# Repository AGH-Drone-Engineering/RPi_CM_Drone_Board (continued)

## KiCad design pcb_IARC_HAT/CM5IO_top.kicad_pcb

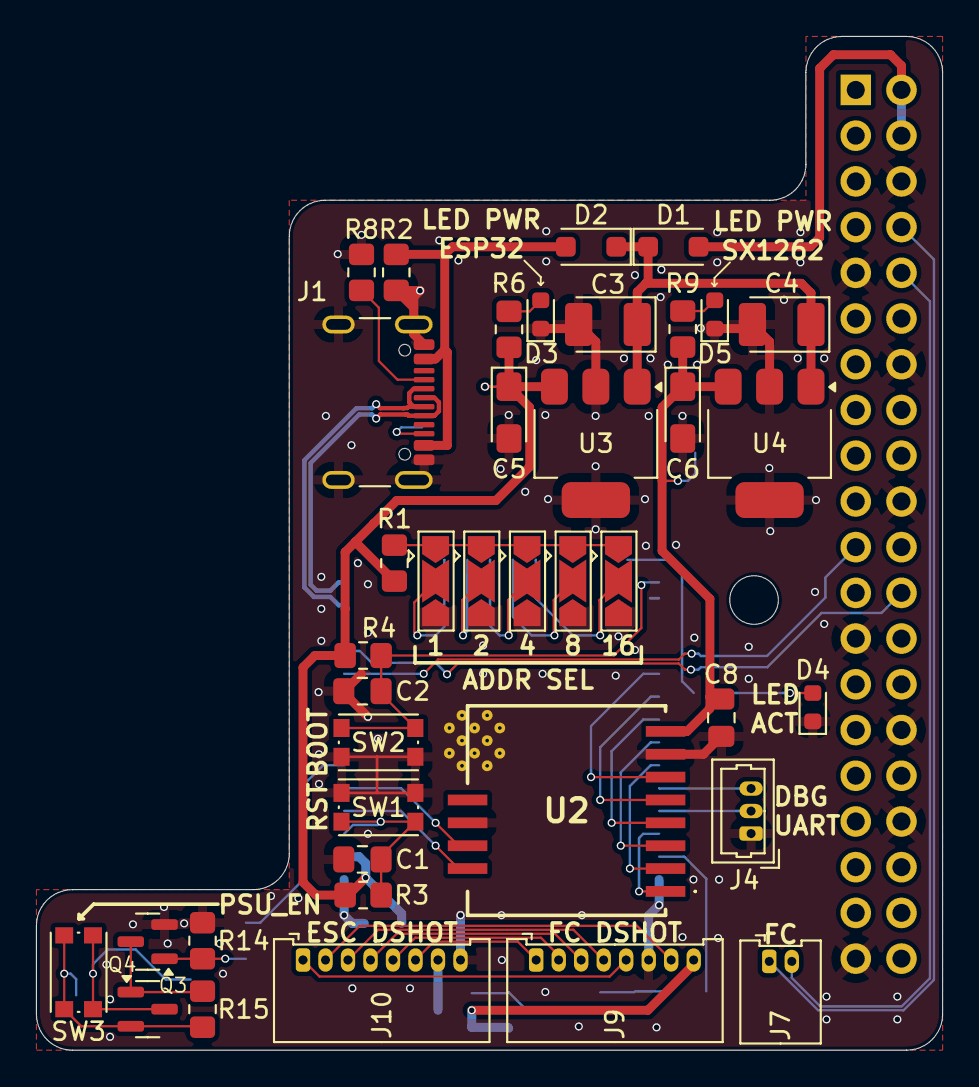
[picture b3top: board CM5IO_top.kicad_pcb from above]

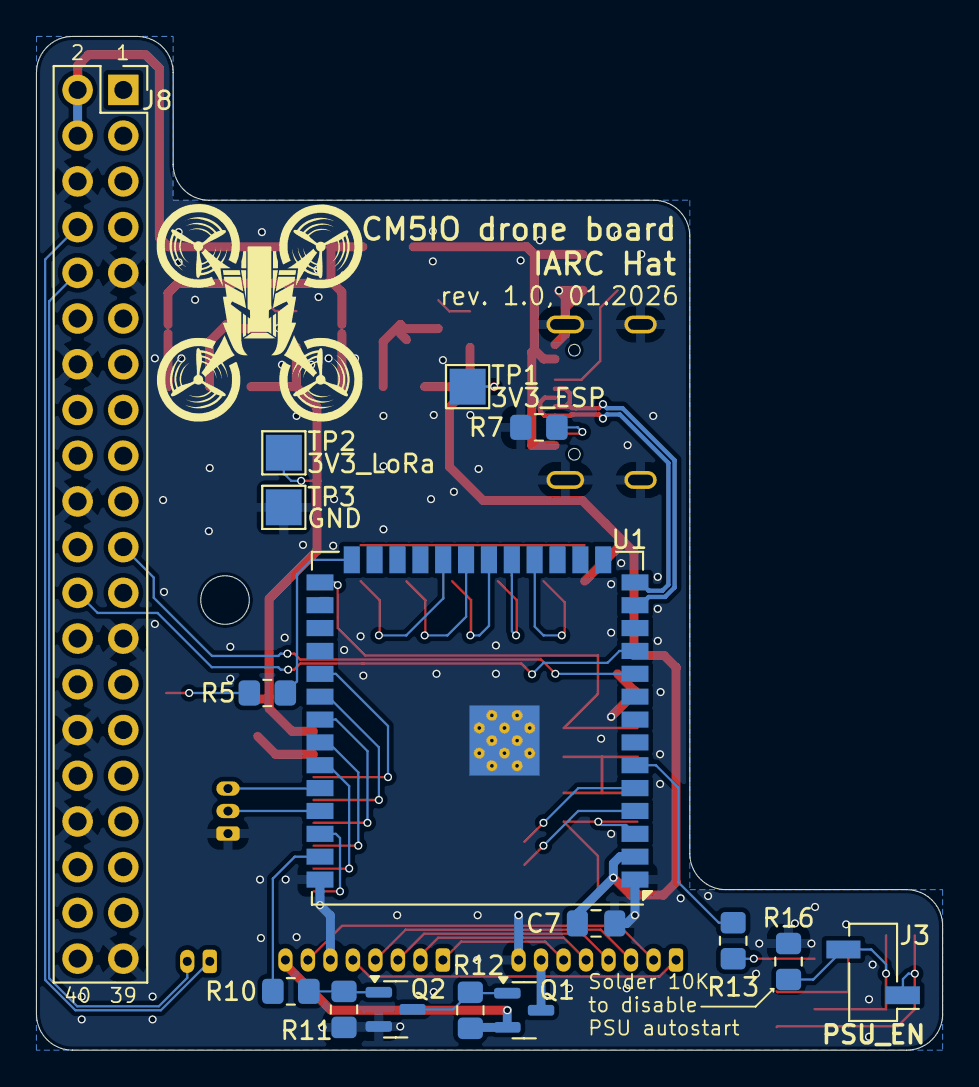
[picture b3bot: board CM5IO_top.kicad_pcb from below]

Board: 2 copper layers, 50.3 x 56.3 mm, 57 parts (16 on the bottom side), 52 nets.

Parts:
C1, C2, C7, C8: 470nF; C_0805_2012Metric_Pad1.18x1.45mm_HandSolder
C3, C4: 4.7uF 35v; CP_EIA-3528-21_Kemet-B_HandSolder
C5, C6: 4.7uF 10v; CP_EIA-3216-18_Kemet-A_HandSolder
D1, D2: MBR1020VL; D_SOD-123F
D3, D5: LED Red; LED_0603_1608Metric
D4: LED Green; LED_0603_1608Metric
H1: MountingHole; MountingHole_2.7mm_M2.5_DIN965
J1: USB_C_Receptacle_USB2.0; USB_C_Receptacle_GCT_USB4105-xx-A_16P_TopMnt_Horizontal
J3: J_PSU_EN; PinSocket_1x02_P2.54mm_Vertical_SMD_Pin1Left
J4: J_ESP_DBG_UART; Molex_PicoBlade_53047-0310_1x03_P1.25mm_Vertical
J7: J_FC_UART; Molex_PicoBlade_53048-0210_1x02_P1.25mm_Horizontal
J8: THD-20-R; PinSocket_2x20_P2.54mm_Vertical
J9: J_DShot600_ESC; Molex_PicoBlade_53048-0810_1x08_P1.25mm_Horizontal
J10: J_DShot600_FC; Molex_PicoBlade_53048-0810_1x08_P1.25mm_Horizontal
JP1: ADDR1; SolderJumper-3_P2.0mm_Open_TrianglePad1.0x1.5mm
JP2: ADDR2; SolderJumper-3_P2.0mm_Open_TrianglePad1.0x1.5mm
JP3: ADDR4; SolderJumper-3_P2.0mm_Open_TrianglePad1.0x1.5mm
JP4: ADDR8; SolderJumper-3_P2.0mm_Open_TrianglePad1.0x1.5mm
JP5: ADDR16; SolderJumper-3_P2.0mm_Open_TrianglePad1.0x1.5mm
Module1: ComputeModule5-CM5; Raspberry-Pi-5-Compute-Module
Q1, Q4: AO3401A; SOT-23
Q2, Q3: Q_NPN_BEC; SOT-23
R1, R3, R4, R5, R6, R9, R10, R12, R13, R15: 1K; R_0805_2012Metric_Pad1.20x1.40mm_HandSolder
R2: 2.2K 1%; R_0805_2012Metric_Pad1.20x1.40mm_HandSolder
R7, R8: 5.1K 1%; R_0805_2012Metric_Pad1.20x1.40mm_HandSolder
R11, R14, R16: 10K; R_0805_2012Metric_Pad1.20x1.40mm_HandSolder
SW1: SW_RESET; SW_Push_1P1T_NO_CK_KMR2
SW2: SW_BOOT; SW_Push_1P1T_NO_CK_KMR2
SW3: FORCE_PWR; SW_Push_1P1T_NO_CK_KMR2
TP1: 3V3_ESP; TestPoint_Pad_2.0x2.0mm
TP2: 3V3_LORA; TestPoint_Pad_2.0x2.0mm
TP3: GND; TestPoint_Pad_2.0x2.0mm
U1: ESP32-S3-WROOM-1; ESP32-S3-WROOM-1U
U2: Wio-SX1262
U3, U4: AP7361C-33E; SOT-223-3_TabPin2

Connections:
/+3.3v_ESP: C5.1, C7.2, R1.1, R3.1, R4.1, R6.1, TP1.1, U1.2 (3V3), U3.3 (VO)
/+3.3v_LoRa: C6.1, C8.2, R9.1, TP2.1, U2.8 (VCC), U4.3 (VO)
/+5v_RPi: D1.2 (A), J8.2, J8.4
/+5v_USB: D2.2 (A), J1.A4 (VBUS), J1.A9 (VBUS), J1.B4 (VBUS), J1.B9 (VBUS), R2.1
/Comm/ADDR1: JP1.2 (C), U1.18 (IO10)
/Comm/ADDR2: JP2.2 (C), U1.19 (IO11)
/Comm/ADDR4: JP3.2 (C), U1.20 (IO12)
/Comm/ADDR8: JP4.2 (C), U1.21 (IO13)
/Comm/ADDR16: JP5.2 (C), U1.22 (IO14)
/Comm/ADDR_HIGH: JP1.1 (A), JP2.1 (A), JP3.1 (A), JP4.1 (A), JP5.1 (A), R1.2
/Comm/BOOT_MODE: C2.2, R4.2, SW2.2, U1.27 (IO0)
/Comm/ENABLE: C1.2, R3.2, SW1.2, U1.3 (EN)
/Comm/KILLSWITCH_FC_CTL: R10.1, U1.39 (IO1)
/Comm/KILLSWITCH_PSU_CTL: R13.1, U1.6 (IO6)
/Comm/LED_ACT: R5.1, U1.26 (IO45)
/Comm/LORA_BUSY: U1.5 (IO5), U2.11 (BUSY)
/Comm/LORA_DIO1: U1.4 (IO4), U2.12 (DIO1)
/Comm/LORA_RESET: U1.32 (IO39), U2.5 (NRST)
/Comm/LORA_RF_SW: U1.38 (IO2), U2.1 (RF_SW_)
/Comm/LORA_SPI_CLK: U1.33 (IO40), U2.4 (SCK)
/Comm/LORA_SPI_CS: U1.31 (IO38), U2.6 (NSS)
/Comm/LORA_SPI_MISO: U1.35 (IO42), U2.2 (MISO)
/Comm/LORA_SPI_MOSI: U1.34 (IO41), U2.3 (MOSI)
/Dshot600_CURR: J9.5, J10.1
/Dshot600_M1: J9.4, J10.3
/Dshot600_M2: J9.3, J10.4
/Dshot600_M3: J9.2, J10.5
/Dshot600_M4: J9.1, J10.6
/Dshot600_R7: J9.7, J10.2
/ESP_USB2_N: J1.A7 (D-), J1.B7 (D-), U1.13 (USB_D-)
/ESP_USB2_P: J1.A6 (D+), J1.B6 (D+), U1.14 (USB_D+)
/GPIO8: J8.24, U1.11 (IO18)
/GPIO9: J8.21, U1.10 (IO17)
/GPIO14_UART_TX: J7.1, J8.8
/GPIO15_UART_RX: J7.2, J8.10
/PSU_CTL_EN: J3.2, Q4.3 (D), R16.1, SW3.1
/PSU_VIN: J3.1, Q4.2 (S), R15.1, SW3.2
/VBUS_ESC: J9.8, Q1.2 (S), R12.1
/VBUS_FC: J10.7, Q1.3 (D)
/VIN: C3.1, C4.1, D1.1 (K), D2.1 (K), U3.1 (VI), U4.1 (VI)
GND: C1.1, C2.1, C3.2, C4.2, C5.2, C6.2, C7.1, C8.1, D3.1 (K), D4.1 (K), D5.1 (K), J1.A1 (GND), J1.A12 (GND), J1.B1 (GND), J1.B12 (GND), J1.S1 (SHIELD), J4.1, J8.6, J8.9, J8.14, J8.20, J8.25, J8.30, J8.34, J8.39, J9.6, J10.8, JP1.3 (B), JP2.3 (B), JP3.3 (B), JP4.3 (B), JP5.3 (B), Q2.2 (E), Q3.2 (E), R2.2, R7.1, R8.1, R11.2, R14.2, R16.2, SW1.1, SW2.1, TP3.1, U1.1 (GND), U1.40 (GND), U1.41 (GND), U2.7 (GND_1), U2.10 (GND_2), U3.2 (GND), U4.2 (GND)
unnamed: D3.2 (A), R6.2
unnamed: D4.2 (A), R5.2
unnamed: D5.2 (A), R9.2
unnamed: J1.A5 (CC1), R8.2
unnamed: J1.B5 (CC2), R7.2
unnamed: J4.2, U1.37 (TXD0)
unnamed: J4.3, U1.36 (RXD0)
unnamed: Q1.1 (G), Q2.3 (C), R12.2
unnamed: Q2.1 (B), R10.2, R11.1
unnamed: Q3.1 (B), R13.2, R14.1
unnamed: Q3.3 (C), Q4.1 (G), R15.2

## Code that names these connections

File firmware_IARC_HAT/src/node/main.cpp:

#include <RFNode.h>
#include <cstring>
#include "UartRfBridge.h"

// Logger write function for USB-CDC (Serial) output.
static void logToUsbCdc(const char *str)
{
    Serial.print(str);
}

static const char *beginStatusToStr(BeginStatus bs)
{
    switch (bs)
    {
    case BeginStatus::OK:
        return "ok";
    case BeginStatus::ALREADY_STARTED:
        return "already_started";
    case BeginStatus::INVALID_CONFIG:
        return "invalid_config";
    case BeginStatus::SECURITY_INIT_FAILED:
        return "security_init_failed";
    case BeginStatus::RADIO_INIT_FAILED:
        return "radio_init_failed";
    case BeginStatus::OUT_OF_MEMORY:
        return "out_of_memory";
    case BeginStatus::NV_NOT_PERSISTENT:
        return "nv_not_persistent";
    case BeginStatus::NV_SEQ_CORRUPTED:
        return "nv_seq_corrupted";
    default:
        return "unknown";
    }
}

// LoRa module pinout on the IARC HAT (SX1262):
#define LORA_CS 38
#define LORA_IRQ 4
#define LORA_RST 39
#define LORA_BUSY 5

#define LORA_RF_SW 2
#define LORA_CLK 40
#define LORA_MOSI 41
#define LORA_MISO 42

// Killswitch pins
#define KILLSWITCH_FC_CTL 1
#define KILLSWITCH_PSU_CTL 6

// RPi <-> ESP link: hardware UART0 (Serial0), remapped off its default pins.
// The module's native TXD0/RXD0 (IO43/IO44, pads 37/36) go to J4
// (J_ESP_DBG_UART), not to the Pi - see pcb_IARC_HAT/comm.kicad_sch. The link
// to the host runs over the 40-pin header J8: net GPIO8 (header pin 24, the
// Pi's TXD3) lands on U1 pad 11 = IO18, and net GPIO9 (header pin 21, the Pi's
// RXD3) on U1 pad 10 = IO17. That is UART3 on the Pi, i.e. /dev/ttyAMA3, which
// is what loracom opens by default.
#define RPI_UART_TX 17
#define RPI_UART_RX 18
#define RPI_UART_BAUD 115200

#define KILL_PAYLOAD "KILL"
static constexpr size_t KILL_PAYLOAD_LEN = sizeof(KILL_PAYLOAD) - 1;

// Only the ground panel may kill
static constexpr uint8_t KILL_MASTER_ADDR = 0xFE;

// Node address is set by the five solder jumpers JP1..JP5 (schematic labels
// ADDR1/2/4/8/16, pcb_IARC_HAT/comm.kicad_sch), least significant bit first.
static const uint8_t ADDR_PINS[] = {10, 11, 12, 13, 14};
static constexpr size_t ADDR_BITS = sizeof(ADDR_PINS) / sizeof(ADDR_PINS[0]);

static SPIClass loraSPI;
static SX1262LoRaRadio radio(SX1262LoRaRadio::Channel::EU868_CH0,
                             LORA_CS, LORA_IRQ, LORA_RST, LORA_BUSY, loraSPI);

// addr is left at its default here and filled in from the jumpers in setup() -
// reading GPIOs during static init would run before the Arduino core is up.
static RFNodeConfig nodeCfg = []()
{
    RFNodeConfig c;
    c.mode = PacketMode::P2P;
    c.security = RFSecurityConfig::FromPassword("bajer");
    c.dutyCycle.enabled = false;
    return c;
}();

// Both need the jumper-derived address, so they're constructed in setup() once
// it's known; loop() reaches them through these.
static RFNode *node = nullptr;
static UartRfBridge *bridge = nullptr;

// Runs on the RF worker task. Safe to call twice - it only ever drives pins low.
static void engageKillswitch()
{
    digitalWrite(KILLSWITCH_FC_CTL, LOW);
    digitalWrite(KILLSWITCH_PSU_CTL, LOW);
}

static uint8_t readAddrJumpers()
{
    for (uint8_t pin : ADDR_PINS)
        pinMode(pin, INPUT_PULLDOWN);
    delay(1); // let the pulldown settle before sampling

    uint8_t addr = 0;
    for (size_t bit = 0; bit < ADDR_BITS; ++bit)
    {
        if (digitalRead(ADDR_PINS[bit]) == HIGH)
            addr |= static_cast<uint8_t>(1u << bit);
    }
    return addr;
}

void setup()
{
    Serial.begin(115200); // USB-CDC: boot/debug diagnostics only
    Logger::setWriteFn(&logToUsbCdc);

    pinMode(KILLSWITCH_FC_CTL, OUTPUT);
    pinMode(KILLSWITCH_PSU_CTL, OUTPUT);
    
    digitalWrite(KILLSWITCH_FC_CTL, LOW);
    digitalWrite(KILLSWITCH_PSU_CTL, HIGH);

    // Default RX ring buffer can't hold a full max-size protocol frame
    Serial0.setRxBufferSize(4096);
    Serial0.begin(RPI_UART_BAUD, SERIAL_8N1, RPI_UART_RX, RPI_UART_TX);
    delay(2000);

    uint8_t myAddr = readAddrJumpers();
    if (myAddr == 0)
    {
        // All five jumpers open/low. Starting with addr 0 would just fail in
        // begin() with a generic invalid_config, so name the real cause.
        LOG_E("main", "boot_error reason=addr_jumpers_unset (JP1..JP5 all low, need addr 1..31)");
        while (1)
            delay(1000);
    }
    nodeCfg.addr = myAddr;

    loraSPI.begin(LORA_CLK, LORA_MISO, LORA_MOSI, LORA_CS);

    static RFNode nodeObj(radio, nodeCfg);
    static UartRfBridge bridgeObj(nodeObj, Serial0, myAddr);
    node = &nodeObj;
    bridge = &bridgeObj;

    // Wire RFNode events to the bridge (handler bodies live in UartRfBridge).
    node->onReceive(
        // A KILL from the ground panel drops both gates; everything reaches the bridge.
        [](const RxInfo &info, const uint8_t *data, size_t len, void *ctx)
        {
            if (info.from == KILL_MASTER_ADDR && !info.broadcast &&
                len == KILL_PAYLOAD_LEN && memcmp(data, KILL_PAYLOAD, KILL_PAYLOAD_LEN) == 0)
            {
                engageKillswitch();
                LOG_W("main", "KILL from 0x%02X — killswitch engaged (FC/PSU low)", info.from);
            }
            UartRfBridge::onReceiveTrampoline(info, data, len, ctx);
        },
        bridge);
    node->onSendOk(UartRfBridge::onSendOkTrampoline, bridge);
    node->onSendFail(UartRfBridge::onSendFailTrampoline, bridge);

    radio.setTransmitProfile(RadioLibLoRaRadio<SX1262>::RfProfile::HIGH_SPEED);

    BeginStatus bs = node->begin();
    if (bs != BeginStatus::OK)
    {
        LOG_E("main", "boot_error reason=%s", beginStatusToStr(bs));
        while (1)
            delay(1000);
    }

    if (!node->startWorkerTask())
    {
        LOG_E("main", "boot_error reason=worker_task_start_failed");
        while (1)
            delay(1000);
    }

    // Radio is up, so the aircraft may have power.
    digitalWrite(KILLSWITCH_FC_CTL, HIGH);
    LOG_I("main", "armed addr=0x%02X (from jumpers) build=%s", myAddr, CMDB_ESP_FIRMWARE_BUILD);
}

void loop()
{
    bridge->poll();
}

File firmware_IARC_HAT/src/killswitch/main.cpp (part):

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}

// LoRa module (SX1262).
#define LORA_CS    38
#define LORA_IRQ    4
#define LORA_RST   39
#define LORA_BUSY   5

#define LORA_RF_SW  2 
#define LORA_CLK   40 
#define LORA_MOSI  41
#define LORA_MISO  42

// I2C to the MCP23017 (U2). R2/R3 (2K2) pull both lines up on the board.
#define I2C_SCL 15
#define I2C_SDA 16

// Front panel. SW_ARM has an internal pullup; the logic treats HIGH as armed.
// Both LEDs are active high.
#define SW_ARM  6
#define LED_ACT 7
#define LED_ARM 48

// SW1 DIP bank, each switch shorts its GPIO to GND when closed.
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#define DIP_SEL7 21
#define DIP_SEL8 47

#define BOOT_MODE 0
#define ESP_TXD0 43
#define ESP_RXD0 44

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
    pinMode(SW_ARM, INPUT_PULLUP);
    pinMode(LED_ARM, OUTPUT);
    pinMode(LED_ACT, OUTPUT);
    digitalWrite(LED_ARM, LOW);
    digitalWrite(LED_ACT, LOW);

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
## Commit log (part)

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2026-01-29 BOM update
2026-02-11 update BOM
2026-04-29 rename directories, update BOM file, cleanup unnecessary files
2026-04-29 board2 image
